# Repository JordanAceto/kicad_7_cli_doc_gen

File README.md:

# Documentation Generator for KiCad 7 Projects

## NOTE: holmesrichards maintains a [much more polished fork](https://gitlab.com/rsholmes/kdocgen) of this script 
- It implements several of the improvements proposed below and adds some nice multi-board-project behavior
- This version is left as-is for now as a basic example of how to use the KiCad 7 `kicad-cli`

## What it is:
- With the introduction of the `kicad-cli` tool in KiCad 7 we can now easily generate many outputs from the command line
- This is a quick and dirty python script that spits out documentation according to my own personal directory structure preference
- It's for Linux operating systems
- It intended as a standalone script, you **don't** need to run this from within the KiCad python terminal
- I imagine it will change and improve over time, this is just a quicky first pass to jot down some ideas, a starting point

## What it produces:
- Schematic PDF
- Interactive HTML BOM
- Basic CSV BOM
- Compressed gerbers and drill files
- PCB layers as PDFs
- Front and back of PCB as SVG
- STEP file of PCB
- If there is no README file for the project directory a simple README is generated

## Dependencies:
- [Interactive HTML BOM](https://github.com/openscopeproject/InteractiveHtmlBom)
  - Must be installed if you want to use it
  - make a symlink to `/usr/local/bin` so we can easily run it from the cli

## Improvements:
- User choice for the outputs
  - Maybe you could feed it some kind of structured JSON/YAML file with your preferences or something
- Detect the PCB stackup and generate the correct layers
- I like to make decorative panels out of PCB material
  - If the project is a panel, adjust the ouputs accordingly (don't need to plot a schematic for a panel, etc)
- There is some bug with the STEP output. It fails to rename the temporary file. The script manually renames it now
- The CSV BOM just runs one of the built in KiCad 7 BOM scripts, this could surely be tweaked for a more personal touch
- The schematic PDF does not use the user's color theme and fonts.
  - The `kicad-cli` help says that it will default to the schematic settings, but it doesn't seem to yet
- It doesn't do any error handling or checking yet
- We could come up with a nicer way of building the command line string for the outputs

## Example:
- Included is an example board which shows the intended project structure
- To get back to a baseline, delete the `docs` directory and `README.md` file in the example
- To generate docs for the example:
  - From the root of this directory `$python kicad_7_doc_gen.py example_board/`
  - Browse the newly generated `docs` directory and `README.me` file

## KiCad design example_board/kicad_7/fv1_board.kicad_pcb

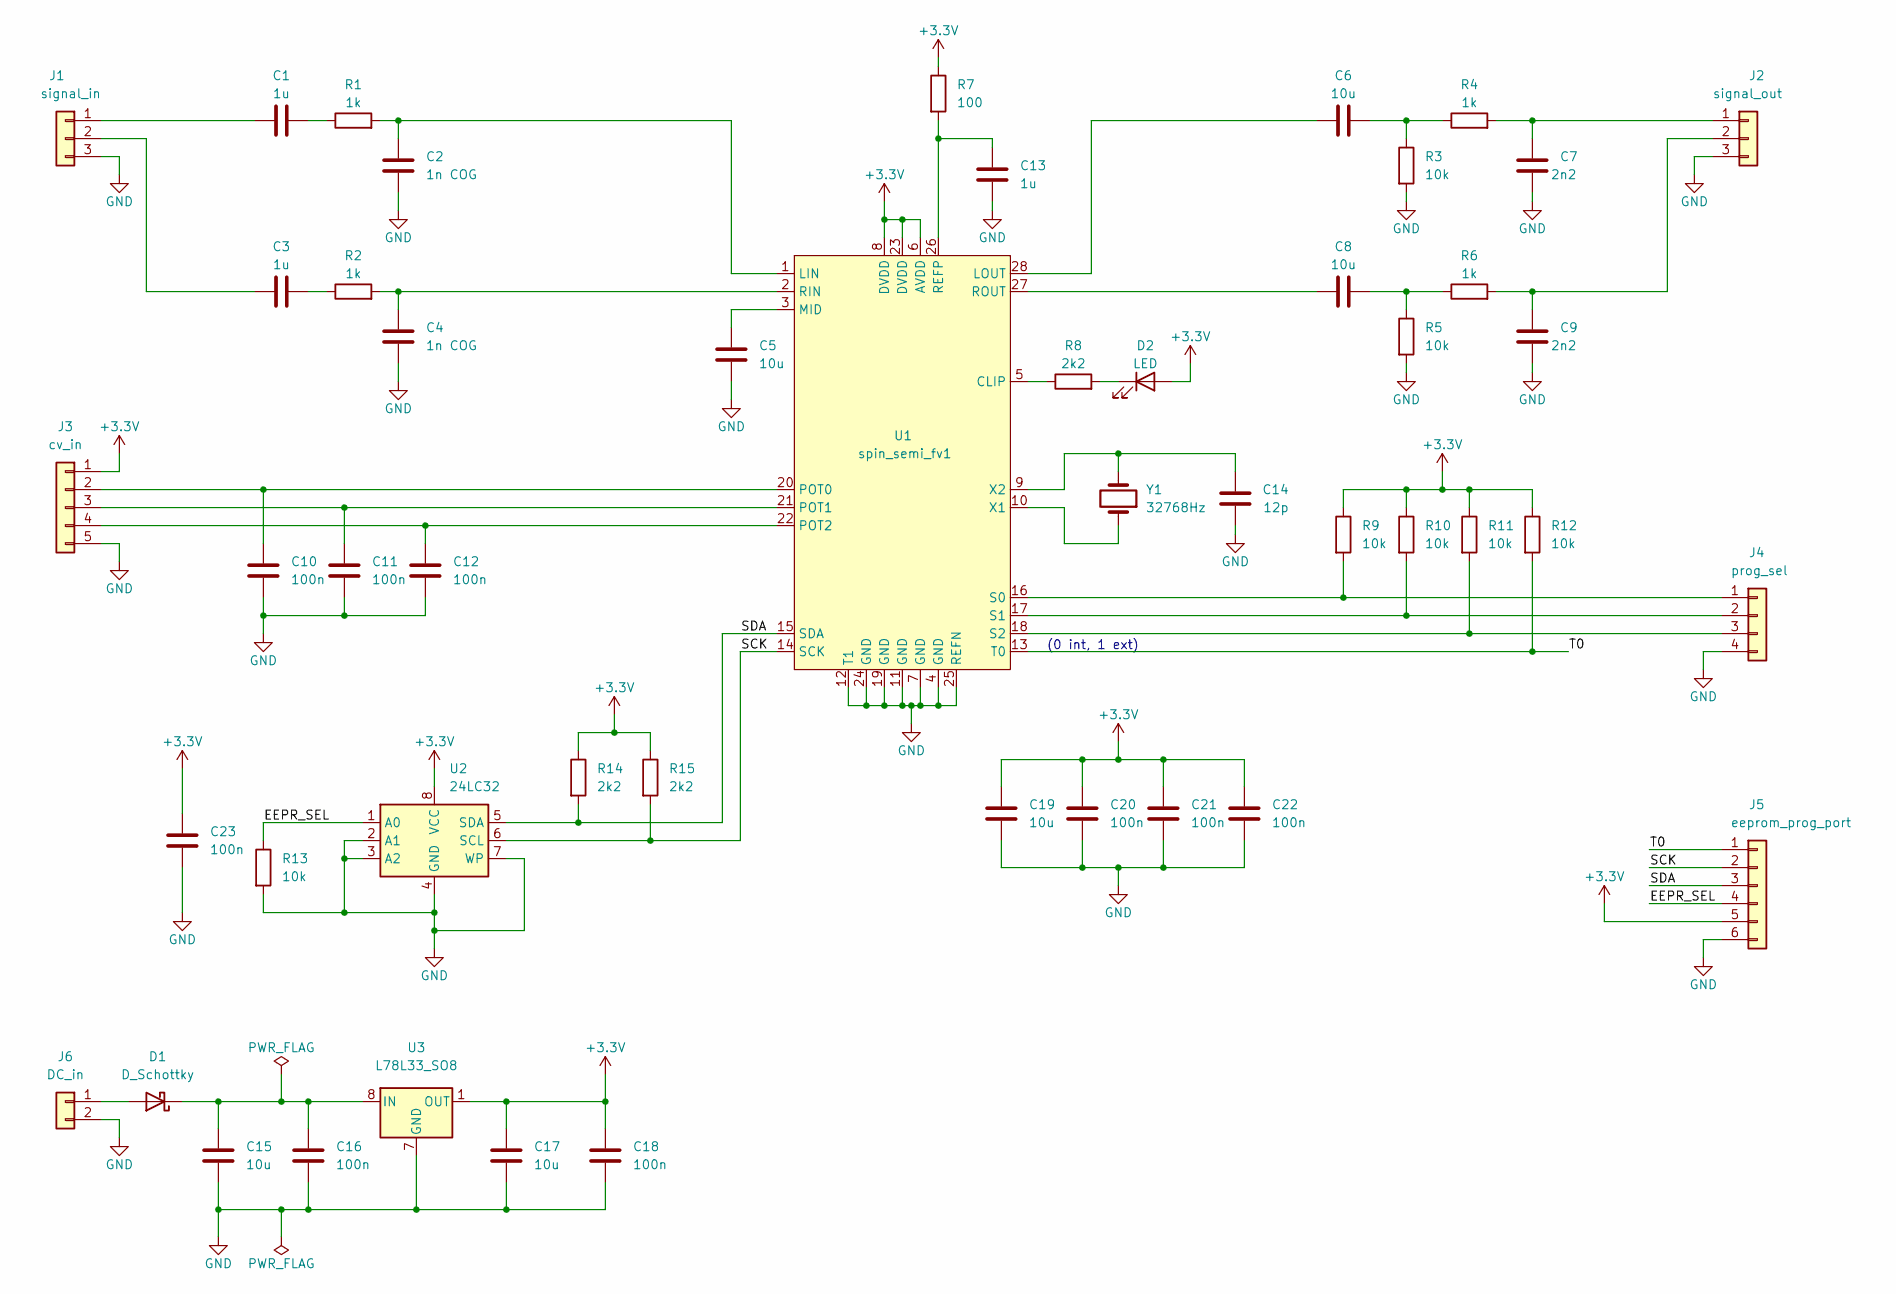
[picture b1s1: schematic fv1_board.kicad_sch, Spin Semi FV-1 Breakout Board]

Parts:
C1, C3, C13: 1u; C_0805_2012Metric
C2, C4: 1n COG; C_0805_2012Metric
C5, C6, C8, C15, C17, C19: 10u; C_0805_2012Metric
C7, C9: 2n2; C_0805_2012Metric
C10, C11, C12, C16, C18, C20, C21, C22, C23: 100n; C_0603_1608Metric
C14: 12p; C_0603_1608Metric
D1: D_Schottky; D_SOD-123
D2: LED; LED_1206_3216Metric
J1: signal_in; PinHeader_1x03_P2.54mm_Vertical
J2: signal_out; PinHeader_1x03_P2.54mm_Vertical
J3: cv_in; PinHeader_1x05_P2.54mm_Vertical
J4: prog_sel; PinHeader_1x04_P2.54mm_Vertical
J5: eeprom_prog_port; PinHeader_1x06_P2.54mm_Vertical
J6: DC_in; PinHeader_1x02_P2.54mm_Vertical
R1, R2, R4, R6: 1k; R_0603_1608Metric
R3, R5, R9, R10, R11, R12, R13: 10k; R_0603_1608Metric
R7: 100; R_0603_1608Metric
R8, R14, R15: 2k2; R_0603_1608Metric
U1: spin_semi_fv1; SOIC-28W_7.5x17.9mm_P1.27mm
U2: 24LC32; DIP-8_W7.62mm_Socket
U3: L78L33_SO8; SOIC-8_3.9x4.9mm_P1.27mm
Y1: 32768Hz; Crystal_C26-LF_D2.1mm_L6.5mm_Horizontal

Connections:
+3.3V: C17.1, C18.1, C19.1, C20.1, C21.1, C22.1, C23.1, D2.2 (A), J3.1, J5.5, R7.1, R9.1, R10.1, R11.1, R12.1, R14.1, R15.1, U1.6 (AVDD), U1.8 (DVDD), U1.23 (DVDD), U2.8 (VCC), U3.1 (OUT)
/EEPR_SEL: J5.4, R13.1, U2.1 (A0)
/SCK: J5.2, R15.2, U1.14 (SCK), U2.6 (SCL)
/SDA: J5.3, R14.2, U1.15 (SDA), U2.5 (SDA)
/T0: J5.1, R12.2, U1.13 (T0)
GND: C2.2, C4.2, C5.2, C7.2, C9.2, C10.2, C11.2, C12.2, C13.2, C14.2, C15.2, C16.2, C17.2, C18.2, C19.2, C20.2, C21.2, C22.2, C23.2, J1.3, J2.3, J3.5, J4.4, J5.6, J6.2, R3.2, R5.2, R13.2, U1.4 (GND), U1.7 (GND), U1.11 (GND), U1.12 (T1), U1.19 (GND), U1.24 (GND), U1.25 (REFN), U2.2 (A1), U2.3 (A2), U2.4 (GND), U2.7 (WP), U3.2 (GND), U3.3 (GND), U3.6 (GND), U3.7 (GND)
unnamed: C1.2, R1.1
unnamed: C3.2, R2.1
unnamed: C6.2, R3.1, R4.1
unnamed: C8.2, R5.1, R6.1
unnamed: D1.2 (A), J6.1
unnamed: C15.1, C16.1, D1.1 (K), U3.8 (IN)
unnamed: D2.1 (K), R8.2
unnamed: C1.1, J1.1
unnamed: C3.1, J1.2
unnamed: C7.1, J2.1, R4.2
unnamed: C9.1, J2.2, R6.2
unnamed: C10.1, J3.2, U1.20 (POT0)
unnamed: C11.1, J3.3, U1.21 (POT1)
unnamed: C12.1, J3.4, U1.22 (POT2)
unnamed: J4.1, R9.2, U1.16 (S0)
unnamed: J4.2, R10.2, U1.17 (S1)
unnamed: J4.3, R11.2, U1.18 (S2)
unnamed: R8.1, U1.5 (CLIP)
unnamed: C2.1, R1.2, U1.1 (LIN)
unnamed: C6.1, U1.28 (LOUT)
unnamed: C5.1, U1.3 (MID)
unnamed: C13.1, R7.2, U1.26 (REFP)
unnamed: C4.1, R2.2, U1.2 (RIN)
unnamed: C8.1, U1.27 (ROUT)
unnamed: U1.10 (X1), Y1.1
unnamed: C14.1, U1.9 (X2), Y1.2

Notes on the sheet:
(0 int, 1 ext)

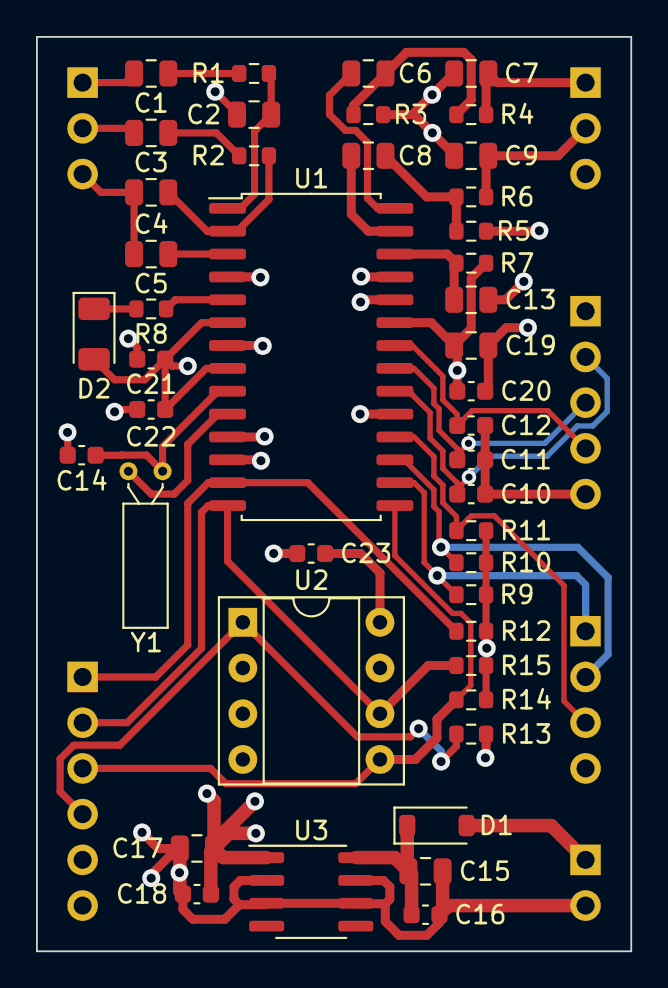
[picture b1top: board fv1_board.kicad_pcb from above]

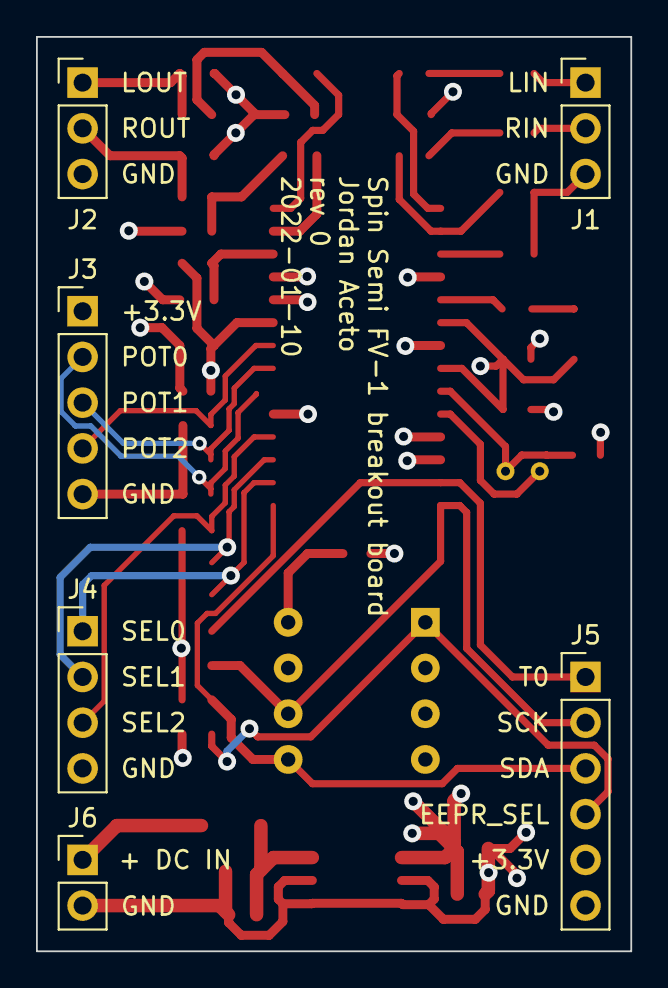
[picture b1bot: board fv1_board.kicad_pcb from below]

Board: 4 copper layers, 33.0 x 50.8 mm, 50 parts (6 on the bottom side), 32 nets.

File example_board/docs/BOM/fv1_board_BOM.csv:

"#","Reference","Qty","Value","Footprint","DNP"
"1","C1, C3, C13","3","1u","Capacitor_SMD:C_0805_2012Metric",""
"2","C2, C4","2","1n COG","Capacitor_SMD:C_0805_2012Metric",""
"3","C5, C6, C8, C15, C17, C19","6","10u","Capacitor_SMD:C_0805_2012Metric",""
"4","C7, C9","2","2n2","Capacitor_SMD:C_0805_2012Metric",""
"5","C10, C11, C12, C16, C18, C20, C21, C22, C23","9","100n","Capacitor_SMD:C_0603_1608Metric",""
"6","C14","1","12p","Capacitor_SMD:C_0603_1608Metric",""
"7","D1","1","D_Schottky","Diode_SMD:D_SOD-123",""
"8","D2","1","LED","LED_SMD:LED_1206_3216Metric",""
"9","J1","1","signal_in","Connector_PinHeader_2.54mm:PinHeader_1x03_P2.54mm_Vertical",""
"10","J2","1","signal_out","Connector_PinHeader_2.54mm:PinHeader_1x03_P2.54mm_Vertical",""
"11","J3","1","cv_in","Connector_PinHeader_2.54mm:PinHeader_1x05_P2.54mm_Vertical",""
"12","J4","1","prog_sel","Connector_PinHeader_2.54mm:PinHeader_1x04_P2.54mm_Vertical",""
"13","J5","1","eeprom_prog_port","Connector_PinHeader_2.54mm:PinHeader_1x06_P2.54mm_Vertical",""
"14","J6","1","DC_in","Connector_PinHeader_2.54mm:PinHeader_1x02_P2.54mm_Vertical",""
"15","R1, R2, R4, R6","4","1k","Resistor_SMD:R_0603_1608Metric",""
"16","R3, R5, R9, R10, R11, R12, R13","7","10k","Resistor_SMD:R_0603_1608Metric",""
"17","R7","1","100","Resistor_SMD:R_0603_1608Metric",""
"18","R8, R14, R15","3","2k2","Resistor_SMD:R_0603_1608Metric",""
"19","U1","1","spin_semi_fv1","Package_SO:SOIC-28W_7.5x17.9mm_P1.27mm",""
"20","U2","1","24LC32","Package_DIP:DIP-8_W7.62mm_Socket",""
"21","U3","1","L78L33_SO8","Package_SO:SOIC-8_3.9x4.9mm_P1.27mm",""
"22","Y1","1","32768Hz","Crystal:Crystal_C26-LF_D2.1mm_L6.5mm_Horizontal",""

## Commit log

2023-02-17 Create LICENCE
2023-03-11 Fix typo in license name
2023-03-11 Update README, point to new fork
2023-03-28 Fix buug where drill files were not generated, remove junk dir structure in compressed gerbers
2024-01-09 Update link to Rich's improved repo, it moved to Gitlab

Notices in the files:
example_board/kicad_7/fv1_board.kicad_pcb:
creativecommons.org/licenses/by-sa/4.0
License: CC-by-SA
